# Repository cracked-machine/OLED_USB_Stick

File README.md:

## OLED-USB Stick

Required Kicad Hardware library: https://github.com/cracked-machine/KicadLibrary

Related SW project: https://github.com/cracked-machine/OLED_USB_Stick_SW

This project was an excuse to play with the FT232RL chips. I thought it would be fun to have a USB stick device that would:

- Take input text from a TTY and send it to an OLED display
- Allow firmware update via the same USB plug.

### Design implementation

There are four LEDs on the top. These indicate:

- USB->UART transmit/receive signals
- USB 5V bus power
- USB Host suspend mode

Note, the I2C connector has pull-up resistors (R6/R7) on the SCL and SDA lines. These are not required when using the OLED module since they are included on the module already. However, adding the pull-up resistors allows a direct interface to the MCU I2C interface. So, if you omit the OLED display, you can talk directly to the onboard MCU using an external device via I2C.

U1 is the FTDI FT232RL and handles the USB->RS232 interface.

U3 is the STM32F051 MCU. It's UART TX/RX IO pins are connected directly to the output of the U1 RXD/TXD IO pins.  A mode switch connects the BOOT0 pin of the MCU to either 3V3 or GND, which initialises the MCU using either the bootloader (sysmem) or user application (flash). When updating the firmware the PRG option should be selected so that the bootloader can be accessed and the user application downloaded to flash. After switching between modes the reset button should be pressed before continuing.

There is also an optional LED (D5) on the back of the PCB to allow quick debug testing, as there is no access to the SWD debug interface.

The 5V USB vbus line is regulated down to 3V3 (via a SOT23 regulator) to supply the MCU.

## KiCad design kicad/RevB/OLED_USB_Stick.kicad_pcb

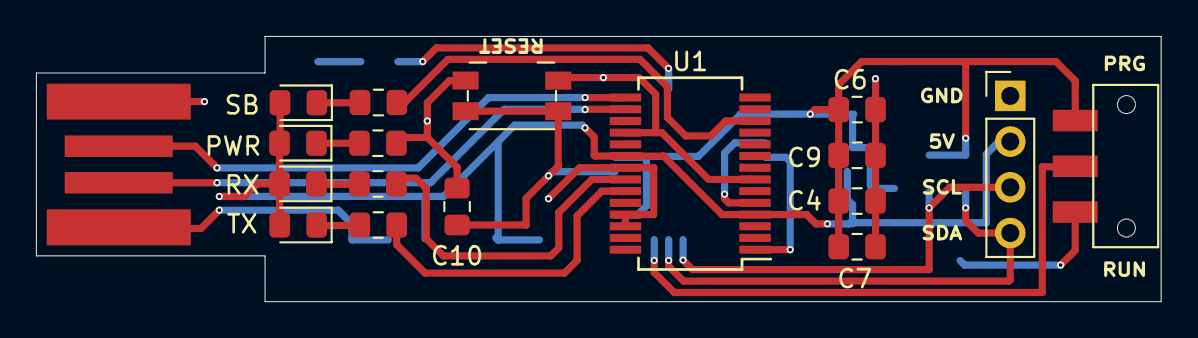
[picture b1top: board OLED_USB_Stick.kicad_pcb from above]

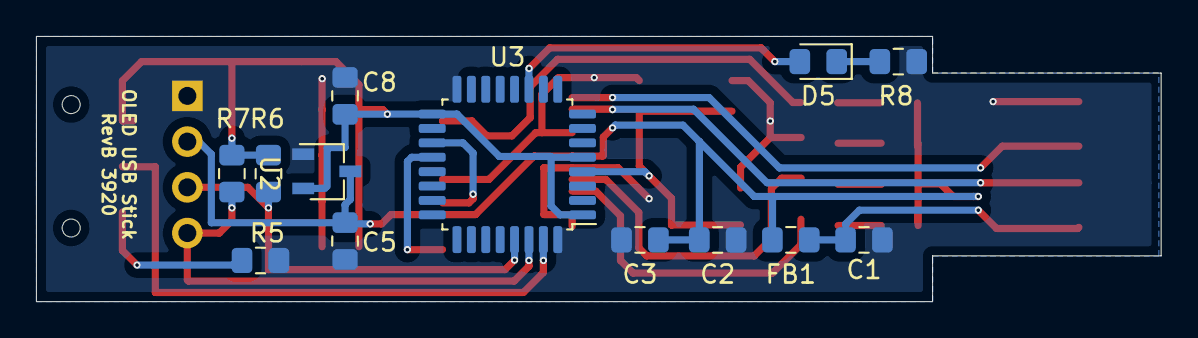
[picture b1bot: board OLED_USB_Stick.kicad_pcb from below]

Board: 2 copper layers, 62.5 x 14.7 mm, 31 parts (13 on the bottom side), 22 nets.

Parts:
C1: 10nF; C_0805_2012Metric_Pad1.15x1.40mm_HandSolder
C2, C6, C7, C9, C10: 100nF; C_0805_2012Metric_Pad1.15x1.40mm_HandSolder
C3: 4.7uF; C_0805_2012Metric_Pad1.15x1.40mm_HandSolder
C4, C5, C8: 1uF; C_0805_2012Metric_Pad1.15x1.40mm_HandSolder
D1: TXLED; LED_0805_2012Metric_Pad1.15x1.40mm_HandSolder
D2: RXLED; LED_0805_2012Metric_Pad1.15x1.40mm_HandSolder
D3: SLEEPLED; LED_0805_2012Metric_Pad1.15x1.40mm_HandSolder
D4: PWRLED; LED_0805_2012Metric_Pad1.15x1.40mm_HandSolder
D5: LED; LED_0805_2012Metric_Pad1.15x1.40mm_HandSolder
FB1: Ferrite_Bead_Small; L_0805_2012Metric_Pad1.15x1.40mm_HandSolder
J1: USB_A; USB_A_Plug_ConnectorLess
J3: Conn_01x04; PinHeader_1x04_P2.54mm_Vertical
R1, R2, R3, R4, R8: 1K; R_0805_2012Metric_Pad1.15x1.40mm_HandSolder
R5, R6, R7: 10K; R_0805_2012Metric_Pad1.15x1.40mm_HandSolder
SW1: SW_SPDT; JS102011SAQN
SW2: SW_SPST; Panasonic_EVQPUK_EVQPUB
U1: FT232RL; SSOP-28_5.3x10.2mm_P0.65mm
U2: SE8233X2; TSOT-23
U3: STM32F051K4Tx; LQFP-32_7x7mm_P0.8mm

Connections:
+3V3: C4.1, C6.1, C7.1, C8.1, C9.1, R6.1, R7.1, SW1.3, U2.2, U3.1, U3.5, U3.17
+5V: C2.2, C3.1, C5.2, D1.2, D2.2, D3.2, D4.2, FB1.2, J3.2, U1.4, U1.20, U2.3
/MCU/I2C_SCL: J3.3, R6.2, U3.29
/MCU/I2C_SDA: J3.4, R7.2, U3.30
/USB_TO_RS232/FT232_RX: U1.5, U3.19
/USB_TO_RS232/FT232_TX: U1.1, U3.20
/USB_TO_RS232/RXLED#: R2.2, U1.22
/USB_TO_RS232/SLEEP#: R3.2, U1.12
/USB_TO_RS232/TXLED#: R1.2, U1.23
GNDS: C1.2, C2.1, C3.2, C4.2, C5.1, C6.2, C7.2, C8.2, C9.2, C10.2, J1.4, J3.1, R4.2, R5.2, R8.2, SW2.1, U1.7, U1.18, U1.21, U1.25, U1.26, U2.1, U3.16, U3.32
unnamed: C1.1, FB1.1, J1.1
unnamed: C10.1, SW2.2, U3.4
unnamed: D1.1, R1.1
unnamed: D2.1, R2.1
unnamed: D3.1, R3.1
unnamed: D4.1, R4.1
unnamed: D5.1, R8.1
unnamed: D5.2, U3.11
unnamed: J1.2, U1.16
unnamed: J1.3, U1.15
unnamed: R5.1, SW1.1
unnamed: SW1.2, U3.31

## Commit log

2020-09-26 first schema draft
2020-09-27 completed RevB
2020-09-27 updated revb hw
    - Added pull up resistors to i2C bus (allows direct connection to mcu from oled port)
2020-09-27 updated docs
    - schema files
2020-09-27 updated hw
    - corrected i2c pins
    - changed reset btn to horizontal mount
